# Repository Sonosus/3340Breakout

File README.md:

View this project on [CADLAB.io](https://cadlab.io/project/25010). 

# 3340Breakout
[![CC BY-SA 4.0][cc-by-sa-shield]][cc-by-sa]

This is a breakout board for the CEM3340/AS3340 chip. It is designed to be relatively simple for beginners to put together and to have flexible mounting options. If you do not require certain features such as pulse width control, hard sync, frequency modulation control, or a triangle, square, or ramp wave, it is possible to omit components so as to avoid the unwanted features.

This work is licensed under a
[Creative Commons Attribution-ShareAlike 4.0 International License][cc-by-sa].

[![CC BY-SA 4.0][cc-by-sa-image]][cc-by-sa]

[cc-by-sa]: http://creativecommons.org/licenses/by-sa/4.0/
[cc-by-sa-image]: https://licensebuttons.net/l/by-sa/4.0/88x31.png
[cc-by-sa-shield]: https://img.shields.io/badge/License-CC%20BY--SA%204.0-lightgrey.svg

This project is certified open source hardware.

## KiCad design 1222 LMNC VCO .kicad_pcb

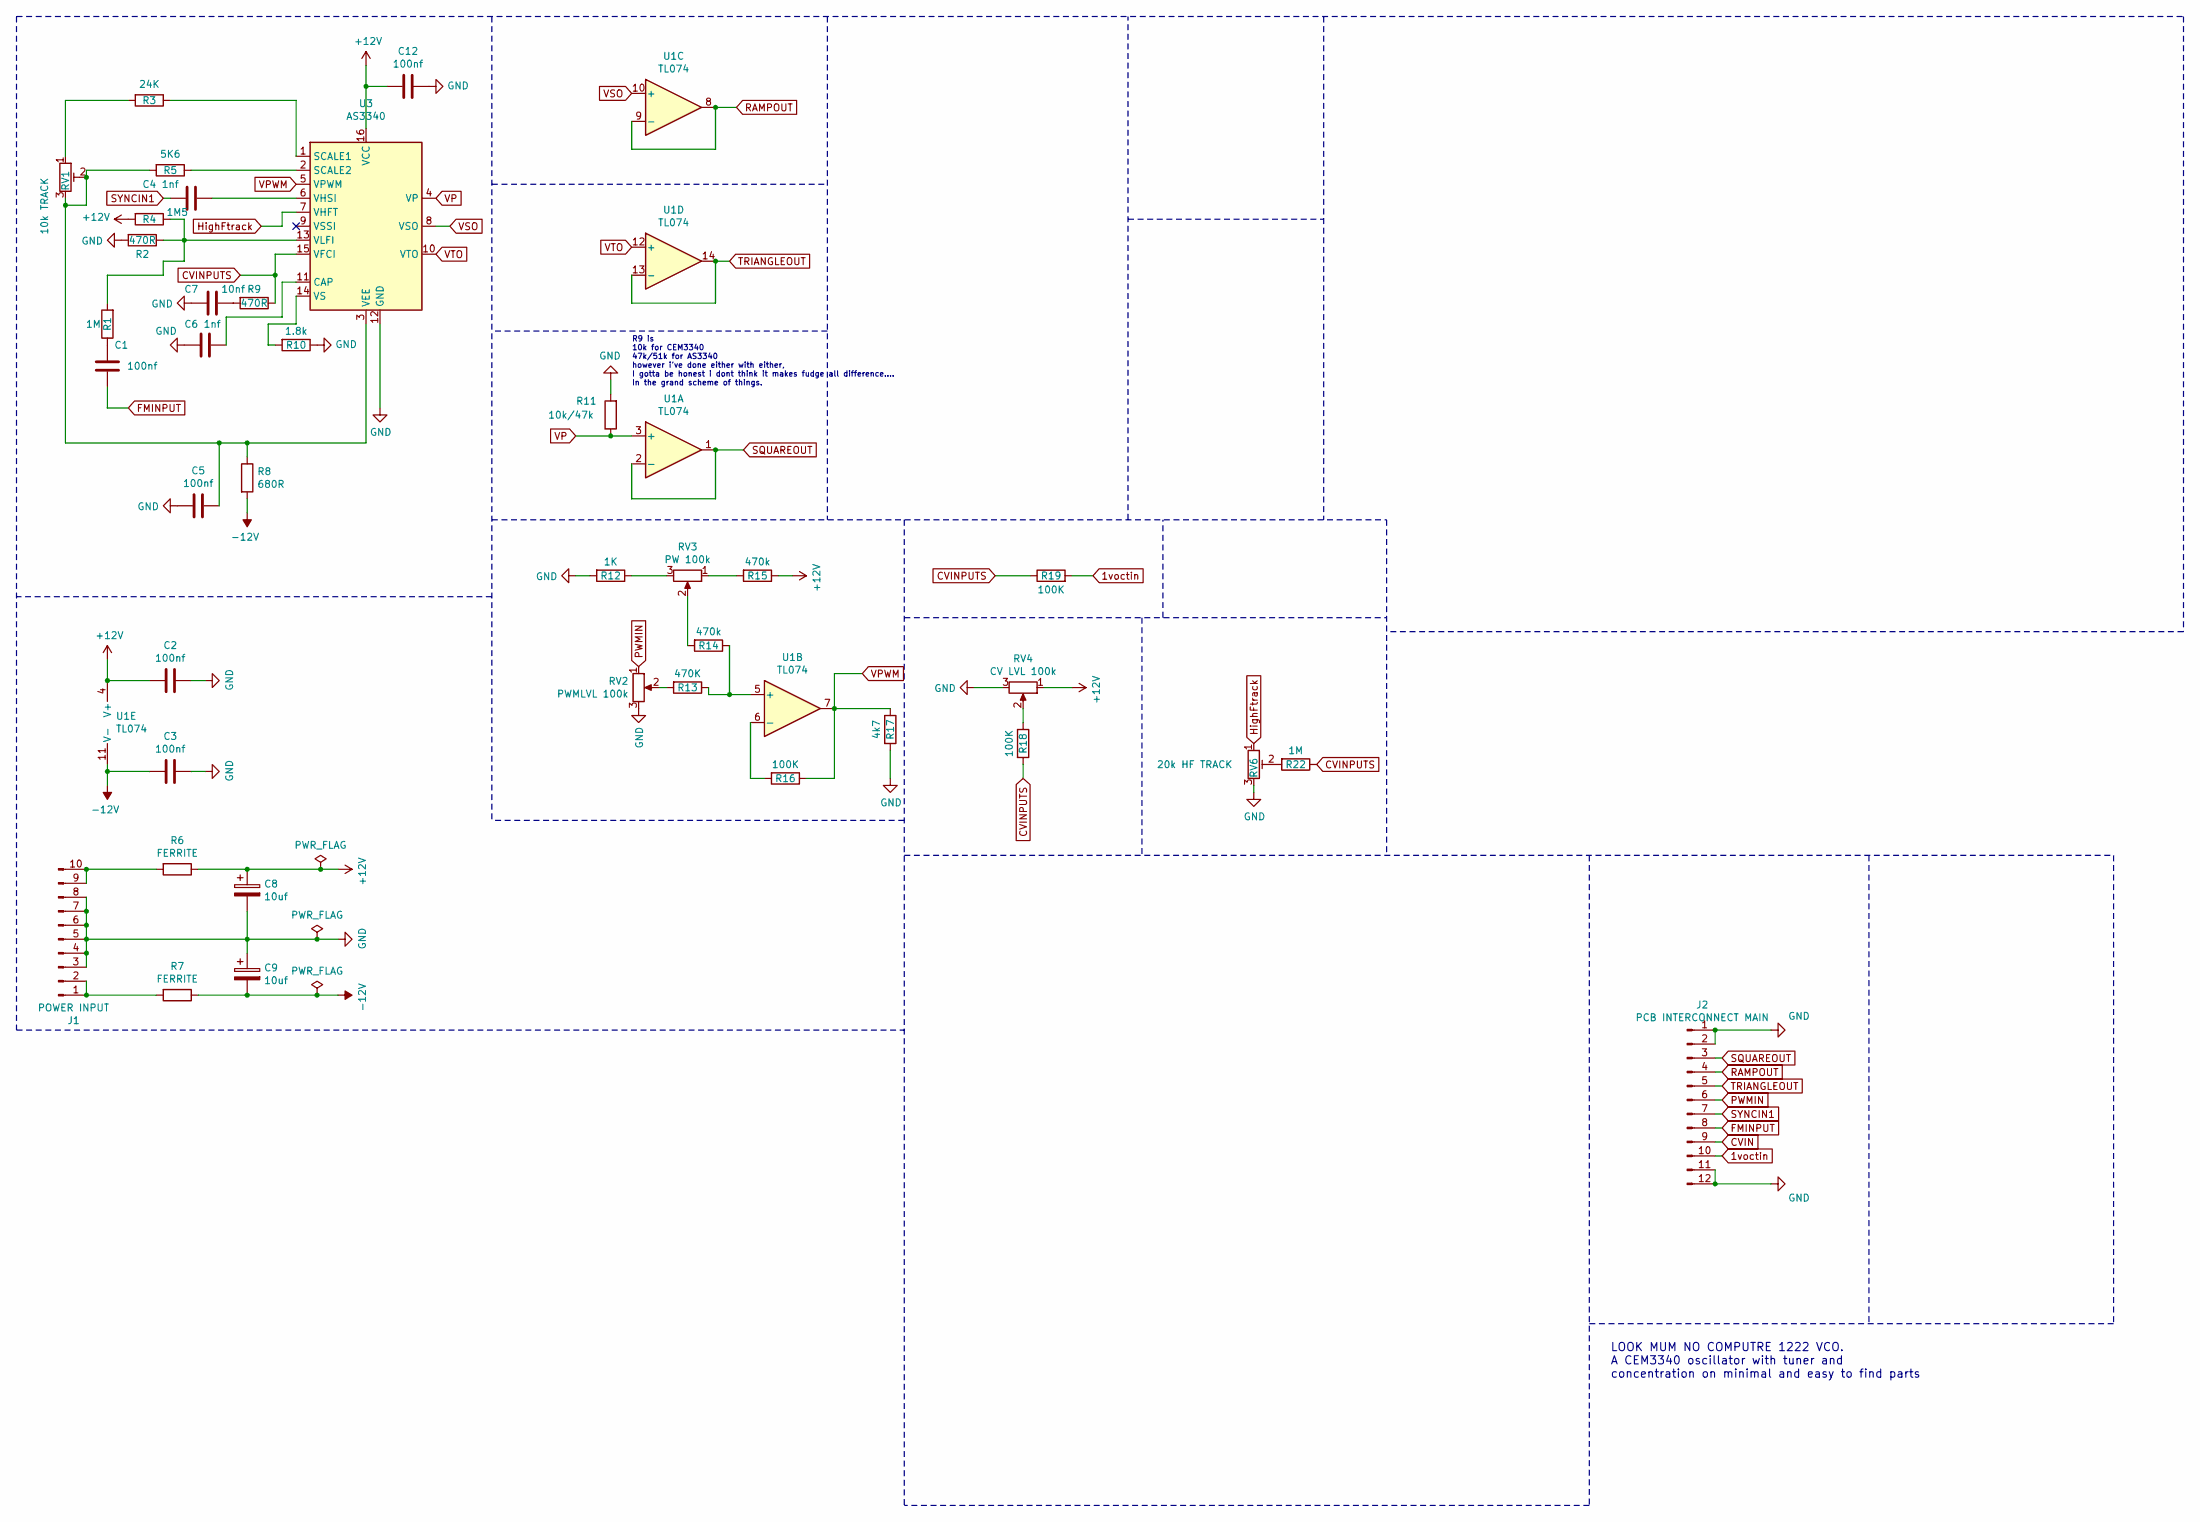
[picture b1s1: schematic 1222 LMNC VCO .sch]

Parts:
C1, C2, C3, C5, C12: 100nf; Capacitor_NonPolarized
C4, C6: 1nf; Capacitor_NonPolarized
C7: 10nf; Capacitor_NonPolarized
C8, C9: 10uf; CP_Radial_D6.3mm_P2.50mm
J1: POWER INPUT; Power_Header
J2: PCB INTERCONNECT MAIN; PinHeader_1x12_P2.54mm_Vertical
R1, R22: 1M; Resistor
R2, R9: 470R; Resistor
R3: 24K; Resistor
R4: 1M5; Resistor
R5: 5K6; Resistor
R6, R7: FERRITE; Resistor
R8: 680R; Resistor
R10: 1.8k; Resistor
R11: 10k/47k; Resistor
R12: 1K; Resistor
R13: 470K; Resistor
R14, R15: 470k; Resistor
R16, R18, R19: 100K; Resistor
R17: 4k7; Resistor
RV1: 10k TRACK; Potentiometer_Bourns_3296W_Vertical
RV2: PWMLVL 100k; PinHeader_1x03_P2.54mm_Vertical
RV3: PW 100k; PinHeader_1x03_P2.54mm_Vertical
RV4: CV LVL 100k; PinHeader_1x03_P2.54mm_Vertical
RV6: 20k HF TRACK; Potentiometer_Bourns_3296W_Vertical
U1: TL074; DIP-14_Socket
U3: AS3340; DIP-16_W7.62mm_Socket_LongPads

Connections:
1voctin: J2.10, R19.2
+12V: C2.2, C8.1, C12.2, R4.2, R6.1, R15.1, RV4.1, U1.4 (V+), U3.16 (VCC); also elsewhere on the board
-12V: C3.2, C9.2, R7.1, R8.2, U1.11 (V-)
CVIN: J2.9
CVINPUTS: R9.1, R18.2, R19.1, R22.1, U3.15 (VFCI)
FMINPUT: C1.1, J2.8
GND: C2.1, C3.1, C5.2, C6.2, C7.2, C8.2, C9.1, C12.1, J1.3, J1.4, J1.5, J1.6, J1.7, J1.8, J2.1, J2.2, J2.11, J2.12, R2.2, R10.1, R11.2, R12.2, R17.2, RV2.3, RV4.3, RV6.3, U3.12 (GND); also elsewhere on the board
HighFtrack: RV6.1, U3.7 (VHFT)
unnamed: C1.2, R1.1
unnamed: C4.1, U3.6 (VHSI)
unnamed: C5.1, R5.2, R8.1, RV1.2, RV1.3, U3.3 (VEE)
unnamed: C6.1, U3.11 (CAP)
unnamed: C7.1, R9.2
unnamed: J1.1, J1.2, R7.2
unnamed: J1.9, J1.10, R6.2
unnamed: R1.2, R2.1, R4.1, U3.13 (VLFI)
unnamed: R3.1, U3.1 (SCALE1)
unnamed: R3.2, RV1.1
unnamed: R5.1, U3.2 (SCALE2)
unnamed: R10.2, U3.14 (VS)
unnamed 20: R12.1, RV3.3; also elsewhere on the board
unnamed: R13.1, R14.1, U1.5 (+)
unnamed 22: R13.2, RV2.2; also elsewhere on the board
unnamed 23: R14.2, RV3.2; also elsewhere on the board
unnamed 24: R15.2, RV3.1; also elsewhere on the board
unnamed: R16.2, U1.6 (-)
unnamed 26: R18.1, RV4.2; also elsewhere on the board
unnamed: R22.2, RV6.2
PWMIN: J2.6, RV2.1; also elsewhere on the board
RAMPOUT: J2.4, U1.8, U1.9 (-)
SQUAREOUT: J2.3, U1.1, U1.2 (-)
SYNCIN1: C4.2, J2.7
TRIANGLEOUT: J2.5, U1.13 (-), U1.14
VP: R11.1, U1.3 (+), U3.4 (VP)
VPWM: R16.1, R17.1, U1.7, U3.5 (VPWM)
VSO: U1.10 (+), U3.8 (VSO)
VTO: U1.12 (+), U3.10 (VTO)

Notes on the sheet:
R9 is 10k for CEM3340 47k/51k for AS3340 however i’ve done either with either, I gotta be honest i dont think it makes fudge all difference…. In the grand scheme of things.
LOOK MUM NO COMPUTRE 1222 VCO. A CEM3340 oscillator with tuner and concentration on minimal and easy to find parts

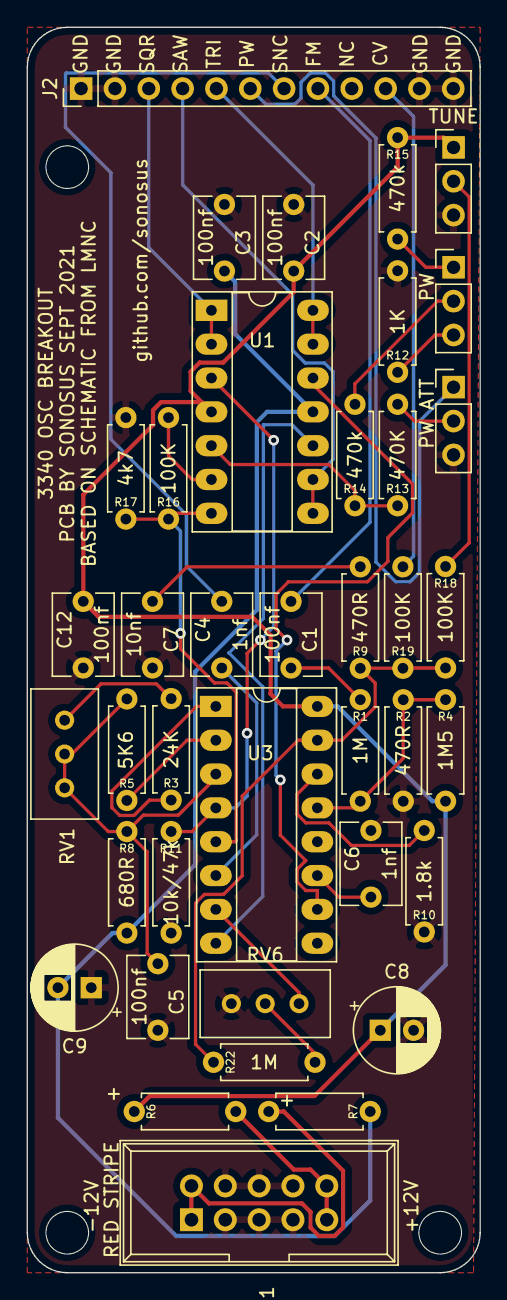
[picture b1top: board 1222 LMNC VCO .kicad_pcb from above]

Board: 2 copper layers, 34.0 x 93.5 mm, 39 parts (0 on the bottom side), 36 nets.

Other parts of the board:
PW: PW 100k; PinHeader_1x03_P2.54mm_Vertical
PW ATT: PWMLVL 100k; PinHeader_1x03_P2.54mm_Vertical
TUNE: CV LVL 100k; PinHeader_1x03_P2.54mm_Vertical

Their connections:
+12V: TUNE.1; also elsewhere on the board
GND: PW ATT.3, TUNE.3; also elsewhere on the board
unnamed 20: PW.3; also elsewhere on the board
unnamed 22: PW ATT.2; also elsewhere on the board
unnamed 23: PW.2; also elsewhere on the board
unnamed 24: PW.1; also elsewhere on the board
unnamed 26: TUNE.2; also elsewhere on the board
PWMIN: PW ATT.1; also elsewhere on the board

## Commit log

2021-10-11 add files
2021-10-11 ibom
2021-10-11 del rescue dcm file
2021-10-11 update schem, plot gerbs again
2021-10-11 plot schem
2021-10-15 Rename svg+xml,_.svg to oshwamark
2021-10-15 Oshw link
2021-10-15 Oshw upload
2021-12-15 Backlink to CADLAB.io has been added.
2022-01-30 rescue
